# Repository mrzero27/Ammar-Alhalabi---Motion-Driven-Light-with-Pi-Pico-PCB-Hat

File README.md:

# Motion-Driven Water Line – Raspberry Pi Pico (Dual Core)

## 1. What the project does

This project runs on a **Raspberry Pi Pico (RP2040)** and drives a **WS2812B (NeoPixel) LED strip** to display a moving “water line” that reacts to the board’s **tilt**.

- If an **MPU-6050** IMU is connected:
  - The code reads accelerometer + gyroscope data over I²C.
  - It computes the **roll angle** (left/right tilt) and uses it to move a “water blob” along the LED strip.
- If **no sensor is present** or it cannot be detected:
  - The code automatically switches to a **simulated motion mode** that generates a smooth sine-wave roll angle.
  - The program still runs and shows the water animation and ASCII output, even on a bare Pico with only USB.

In all cases:

- A **NeoPixel strip** shows a blue-green “water blob” that sits around the middle and moves left/right with tilt, with soft edges and a small shimmer effect.
- An **ASCII visualization** of the water line is printed to the **Serial Monitor** once per frame, together with live sensor/simulation values.

---

## 2. How to test it (with or without hardware)

### 2.1 With full hardware (Pico + MPU-6050 + WS2812B)

**Connections (default, matching the code):**

**MPU-6050 → Pico (I²C)**

- `VCC` → `3V3(OUT)`
- `GND` → `GND`
- `SDA` → `GP4`
- `SCL` → `GP5`
- `AD0` → `GND` (so the address is `0x68` as used in the code)

**WS2812B LED strip → Pico**

- `DIN` → `GP2`
- `GND` → `GND`
- `VCC` → 5 V or 3.3 V (according to your strip’s requirements; GND must be common with Pico)

**Test procedure:**

1. Connect the Pico to the PC via USB.
2. Open the Arduino sketch and upload it using **Arduino IDE** (board set to **Raspberry Pi Pico**, baud rate 115200).
3. Open **Serial Monitor** at **115200 baud**.
4. On startup, you should see something like:

   ```text
   MPU-6050 detected, using real sensor.

5. Now gently tilt the board left and right:

   * The **roll angle** in the Serial Monitor should change sign and magnitude.
   * The **ASCII water bar** in Serial should move left/right accordingly.
   * The **water blob on the NeoPixel strip** should visually follow the tilt.

This demonstrates the full behavior with real sensor data.

---

### 2.2 Without IMU / without custom PCB (simulation mode)

You can still run and test the project **without any external hardware**:

1. Connect only the **Pico + USB** to your PC (no MPU, no LEDs required).
2. Upload the sketch.
3. Open the **Serial Monitor** at **115200 baud**.

If the IMU is not found, you will see:

```text
MPU-6050 NOT found, falling back to simulated motion.
```

After that:

* The code generates a **simulated roll angle** using a sine wave (no sensor needed).
* Every frame it prints:

  * The simulated roll angle.
  * Fixed accelerometer values (`ax, ay, az`).
  * `src=SIM` to indicate simulation mode.
  * The ASCII water bar, which moves smoothly left/right over time.

If you connect only a **NeoPixel strip** (and no IMU), you will also see the LED water animation driven by the same simulated motion.

This way the project is fully testable both:

* **With real hardware** (IMU + LEDs).
* **With no hardware at all** (bare Pico + Serial Monitor).

---

## 3. How each core is used

The Raspberry Pi Pico has two cores. This project explicitly splits responsibilities:

### Core 0 – Sensor / Simulation and Shared State

Core 0 runs the standard Arduino `setup()` and `loop()` functions.

**Responsibilities:**

* Initialize:

  * Serial at 115200 baud.
  * I²C (using `Wire.setSDA(4)` and `Wire.setSCL(5)`).
  * The MPU-6050 (if present) by pinging its I²C address and waking it from sleep.
  * The NeoPixel strip (pin `GP2`, `LED_COUNT = 24`).
  * Launch **Core 1** using `multicore_launch_core1(core1Task);`.

* In `loop()` (every `SENSOR_INTERVAL_MS = 10 ms`):

  1. Create a local `MotionSample` struct.
  2. If the IMU is present and `readMPU6050(...)` succeeds:

     * Read raw accel/gyro registers.
     * Convert raw values to physical units:

       * Accel in g (`raw / 16384.0`).
       * Gyro in deg/s (`raw / 131.0`).
     * Compute the **roll angle**:
       `rollDeg = atan2(ay, az) * 180 / PI;`
     * Mark `sensorOk = true`.
  3. Otherwise:

     * Call `generateSimulatedMotion(...)` to compute a **sine-wave roll angle** (±30°) with fixed accel values.
     * Mark `sensorOk = false` (simulation mode).
  4. Store the resulting `MotionSample` into the global `g_motion` struct, which is shared with Core 1.

**Summary:** Core 0 is responsible for **“what is the current motion?”**, using either real IMU data or a simulated pattern, and publishes that as a shared state.

---

### Core 1 – LED Rendering and ASCII Output

Core 1 runs the `core1Task()` function in parallel.

**Responsibilities (every `FRAME_INTERVAL_MS = 50 ms`):**

1. Copy the shared `g_motion` into a local variable inside a `noInterrupts()/interrupts()` block to avoid partial updates.
2. Take `rollDeg` from the motion sample and map it to a normalized tilt value in **[-1, 1]** using `mapRollToTilt()`:

   * Clamp roll to ±45°.
   * Divide by 45° to get −1…+1.
3. Call `updateLeds(tiltNorm)`:

   * Compute a **center index** along the LED strip based on the tilt.
   * Reflect the center when it would move off the ends (simple “bounce” effect).
   * Apply a **soft radius** around the center to create a blob (triangular falloff).
   * Add a small **shimmer** (time-based modulation) to make the water look alive.
   * Set NeoPixel colors to a blue-ish water tone and call `strip.show()`.
4. Call `buildAsciiWaterLine(tiltNorm)`:

   * Use the same conceptual center and radius over a string of length `LED_COUNT` (or 20 as fallback).
   * Write:

     * `O` at the center.
     * `~` and `-` around the center within the radius.
     * `_` elsewhere.
   * Returns a single-line ASCII representation of the water.
5. Print a single line to Serial combining:

   * Roll angle.
   * `ax, ay, az`.
   * The source (`MPU` or `SIM`).
   * The ASCII water bar.

**Summary:** Core 1 is responsible for **visualization**, both on the **LED strip** and in the **Serial Monitor**, using the motion state produced by Core 0.

---

## 4. Sample Serial Monitor output

### Example with a detected MPU-6050 (real sensor data)

```text
MPU-6050 detected, using real sensor.
roll=-7.5 deg | ax=0.01g ay=-0.13g az=0.98g | src=MPU | water: ____---~~O~~---_________
roll= 0.2 deg | ax=0.00g ay= 0.00g az=1.00g | src=MPU | water: ______---~~O~~---_______
roll=18.9 deg | ax=0.03g ay= 0.32g az=0.94g | src=MPU | water: _________---~~O~~---____
```

### Example in simulation mode (no IMU / not detected)

```text
MPU-6050 NOT found, falling back to simulated motion.
roll=  9.4 deg | ax=0.00g ay=0.00g az=1.00g | src=SIM | water: _______---~~O~~---______
roll= 28.1 deg | ax=0.00g ay=0.00g az=1.00g | src=SIM | water: __________---~~O~~--___
roll= -5.6 deg | ax=0.00g ay=0.00g az=1.00g | src=SIM | water: ____---~~O~~---_________
```

Field meanings:

* `roll`: roll angle in degrees (negative = tilt one way, positive = tilt the other).
* `ax, ay, az`: acceleration components in g.
* `src`:

  * `MPU` = real MPU-6050 readings.
  * `SIM` = internal simulated motion.
* `water`: ASCII representation of the LED strip:

  * `O` = center of the blob.
  * `~` and `-` = body and edges of the water.
  * `_` = empty space.

---

## 5. PCB Layout & 3D Views

### 5.1 Top 3D view – Pico plugged into the hat

This render shows the **Raspberry Pi Pico** plugged into the custom hat.
You can see the **stacking headers** on both sides, the LEDs along the Pico edge, and the overall mechanical outline with four mounting holes.
The silkscreen at the bottom credits the designer and clearly labels the board.

---

### 5.2 Bottom 3D view – IMU and passives

This is the **bottom side** of the PCB.
In the middle you can see the **MPU-6050** IMU and its surrounding capacitors and resistors (decoupling and pull-ups).
The four long female headers give access to all Pico GPIO pins while keeping the IMU wiring short and symmetric.

---

### 5.3 Top copper/layout view – routing and keep-out

This 2D layout view shows the **copper pours, traces and keep-out area** under the Pico’s antenna.
You can see how the I²C lines from the Pico are routed cleanly to the IMU, how the ground pour ties everything together, and how the four mounting holes define the mechanical footprint.

---

### 5.4 Schematic – Pico, IMU and indicators

The schematic shows the overall design:

* On the left, the **MPU-6050** with its power decoupling capacitors, I²C pull-up resistors and address pin configuration.
* At the top, **SDA/SCL indicator LEDs** with series resistors so you can visually see I²C activity.
* On the right, the **Raspberry Pi Pico** with both 20-pin headers broken out and power rails (3V3, VSYS/VBUS, GND) distributed to the connectors.

These four images together document how the PCB implements the firmware concept in hardware: Pico in the center, IMU close and quiet, and all GPIOs still available through the side headers.

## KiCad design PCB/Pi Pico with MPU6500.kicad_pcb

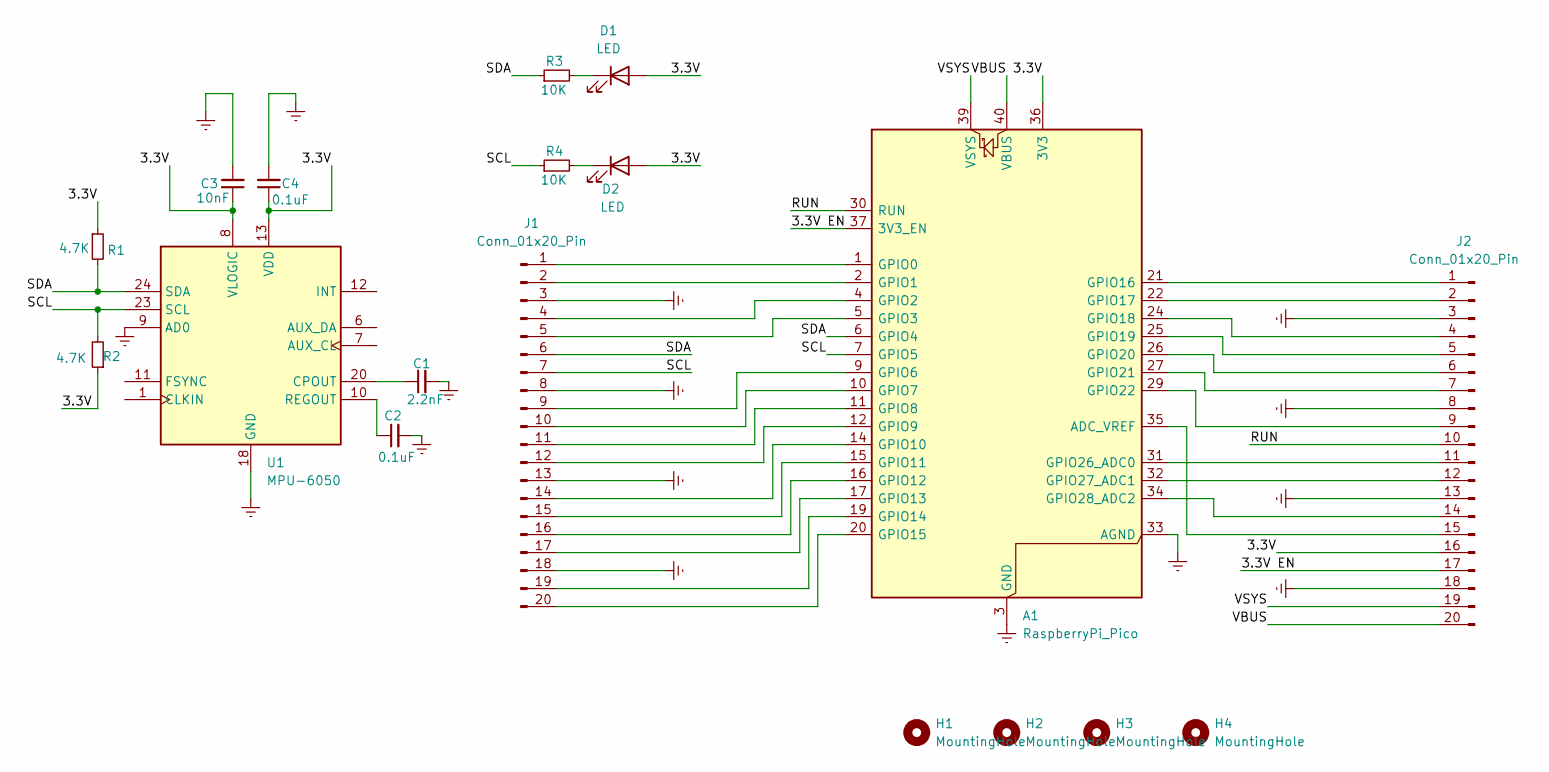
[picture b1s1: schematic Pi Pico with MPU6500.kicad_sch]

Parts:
A1: RaspberryPi_Pico; RaspberryPi_Pico_Common_THT
C1: 2.2nF; C_0603_1608Metric
C2, C4: 0.1uF; C_0603_1608Metric
C3: 10nF; C_0603_1608Metric
D1, D2: LED; LED_0603_1608Metric
H1, H2, H3, H4: MountingHole; MountingHole_3.2mm_M3
J1, J2: Conn_01x20_Pin; PinHeader_1x20_P2.54mm_Vertical
R1, R2: 4.7K; R_0603_1608Metric_Pad0.98x0.95mm_HandSolder
R3, R4: 10K; R_0603_1608Metric_Pad0.98x0.95mm_HandSolder
U1: MPU-6050; InvenSense_QFN-24_4x4mm_P0.5mm

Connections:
/3.3V: A1.36 (3V3), C3.1, C4.1, D1.2 (A), D2.2 (A), J2.16, R1.1, R2.1, U1.8 (VLOGIC), U1.13 (VDD)
/3.3V EN: A1.37 (3V3_EN), J2.17
/RUN: A1.30 (RUN), J2.10
/SCL: A1.7 (GPIO5), J1.7, R2.2, R4.1, U1.23 (SCL)
/SDA: A1.6 (GPIO4), J1.6, R1.2, R3.1, U1.24 (SDA)
/VBUS: A1.40 (VBUS), J2.20
/VSYS: A1.39 (VSYS), J2.19
Earth: A1.3 (GND), A1.8 (GND), A1.13 (GND), A1.18 (GND), A1.23 (GND), A1.28 (GND), A1.33 (AGND), A1.38 (GND), C1.2, C2.2, C3.2, C4.2, J1.3, J1.8, J1.13, J1.18, J2.3, J2.8, J2.13, J2.18, U1.9 (AD0), U1.18 (GND)
unnamed: A1.35 (ADC_VREF), J2.15
unnamed: A1.1 (GPIO0), J1.1
unnamed: A1.2 (GPIO1), J1.2
unnamed: A1.4 (GPIO2), J1.4
unnamed: A1.5 (GPIO3), J1.5
unnamed: A1.9 (GPIO6), J1.9
unnamed: A1.10 (GPIO7), J1.10
unnamed: A1.11 (GPIO8), J1.11
unnamed: A1.12 (GPIO9), J1.12
unnamed: A1.14 (GPIO10), J1.14
unnamed: A1.15 (GPIO11), J1.15
unnamed: A1.16 (GPIO12), J1.16
unnamed: A1.17 (GPIO13), J1.17
unnamed: A1.19 (GPIO14), J1.19
unnamed: A1.20 (GPIO15), J1.20
unnamed: A1.21 (GPIO16), J2.1
unnamed: A1.22 (GPIO17), J2.2
unnamed: A1.24 (GPIO18), J2.4
unnamed: A1.25 (GPIO19), J2.5
unnamed: A1.26 (GPIO20), J2.6
unnamed: A1.27 (GPIO21), J2.7
unnamed: A1.29 (GPIO22), J2.9
unnamed: A1.31 (GPIO26_ADC0), J2.11
unnamed: A1.32 (GPIO27_ADC1), J2.12
unnamed: A1.34 (GPIO28_ADC2), J2.14
unnamed: D1.1 (K), R3.2
unnamed: D2.1 (K), R4.2
unnamed: C1.1, U1.20 (CPOUT)
unnamed: C2.1, U1.10 (REGOUT)

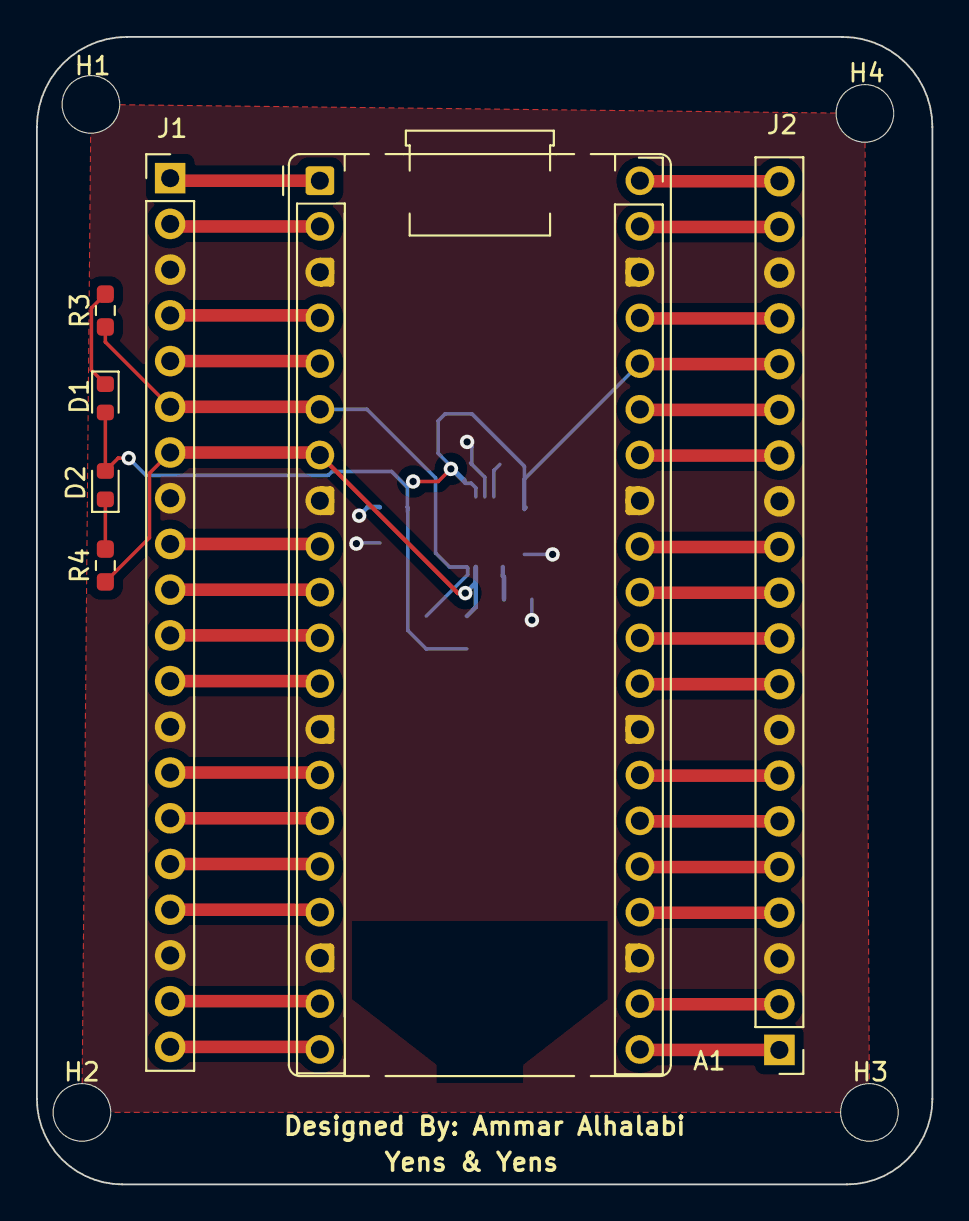
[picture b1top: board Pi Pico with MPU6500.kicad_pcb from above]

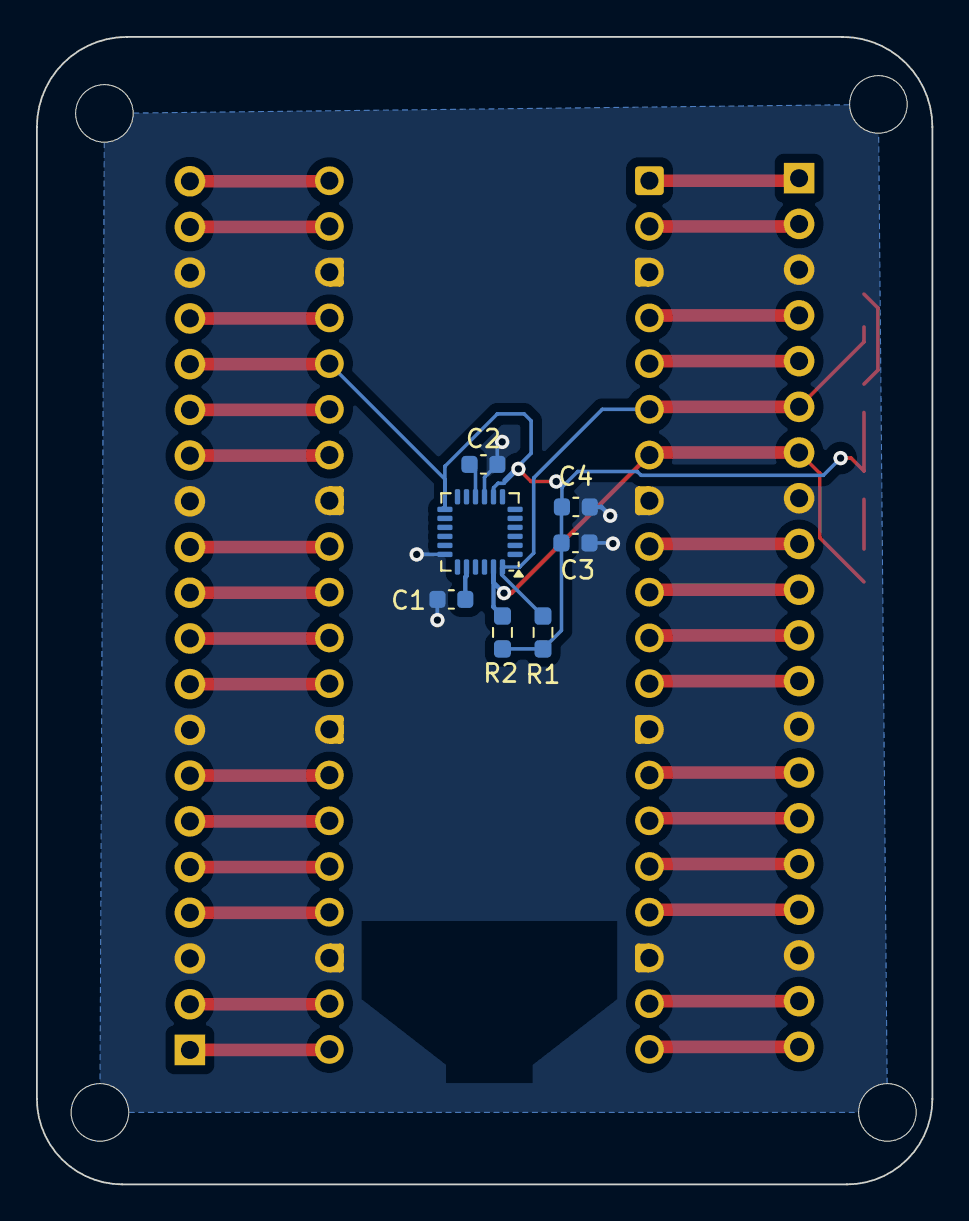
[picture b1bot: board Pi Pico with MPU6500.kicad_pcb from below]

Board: 2 copper layers, 49.8 x 63.8 mm, 18 parts (7 on the bottom side), 37 nets.
